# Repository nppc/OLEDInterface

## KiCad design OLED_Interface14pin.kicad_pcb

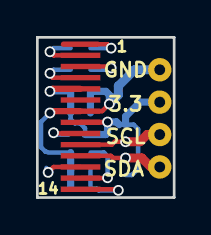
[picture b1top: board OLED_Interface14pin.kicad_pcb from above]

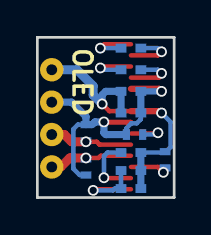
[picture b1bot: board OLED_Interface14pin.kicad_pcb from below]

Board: 2 copper layers, 7.6 x 8.9 mm, 13 parts (11 on the bottom side), 12 nets.

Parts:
C1, C7: 100n; C_0402_NoSilk
C2: 2.2uf; C_0402_NoSilk
C3, C5: 4.7uf; C_0402_NoSilk
C4, C6: 1uf; C_0402_NoSilk
J1: INT; conn_4pin_TH_1.8mm
J2: OLED; OLED_14pin
R1, R2, R4: 4K7; R_0402_NoSilk
R3: 820K; R_0402_NoSilk

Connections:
+3V3: C1.1, C3.1, J1.2, J2.5, J2.8, R1.2, R2.2, R4.2
GND: C1.2, C2.2, C3.2, C5.2, C7.2, J1.1, J2.7, R3.2
unnamed: C2.1, J2.13
unnamed: C4.1, J2.3
unnamed: C4.2, J2.4
unnamed: C5.1, C7.1, J2.14
unnamed: C6.1, J2.1
unnamed: C6.2, J2.2
unnamed: J1.3, J2.10, R1.1
unnamed: J1.4, J2.11, R2.1
unnamed: J2.9, R4.1
unnamed: J2.12, R3.1

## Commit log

2017-10-10 Initial upload
2017-10-10 Parts placement image
2021-07-15 Adding capacitor to RST for proper init
